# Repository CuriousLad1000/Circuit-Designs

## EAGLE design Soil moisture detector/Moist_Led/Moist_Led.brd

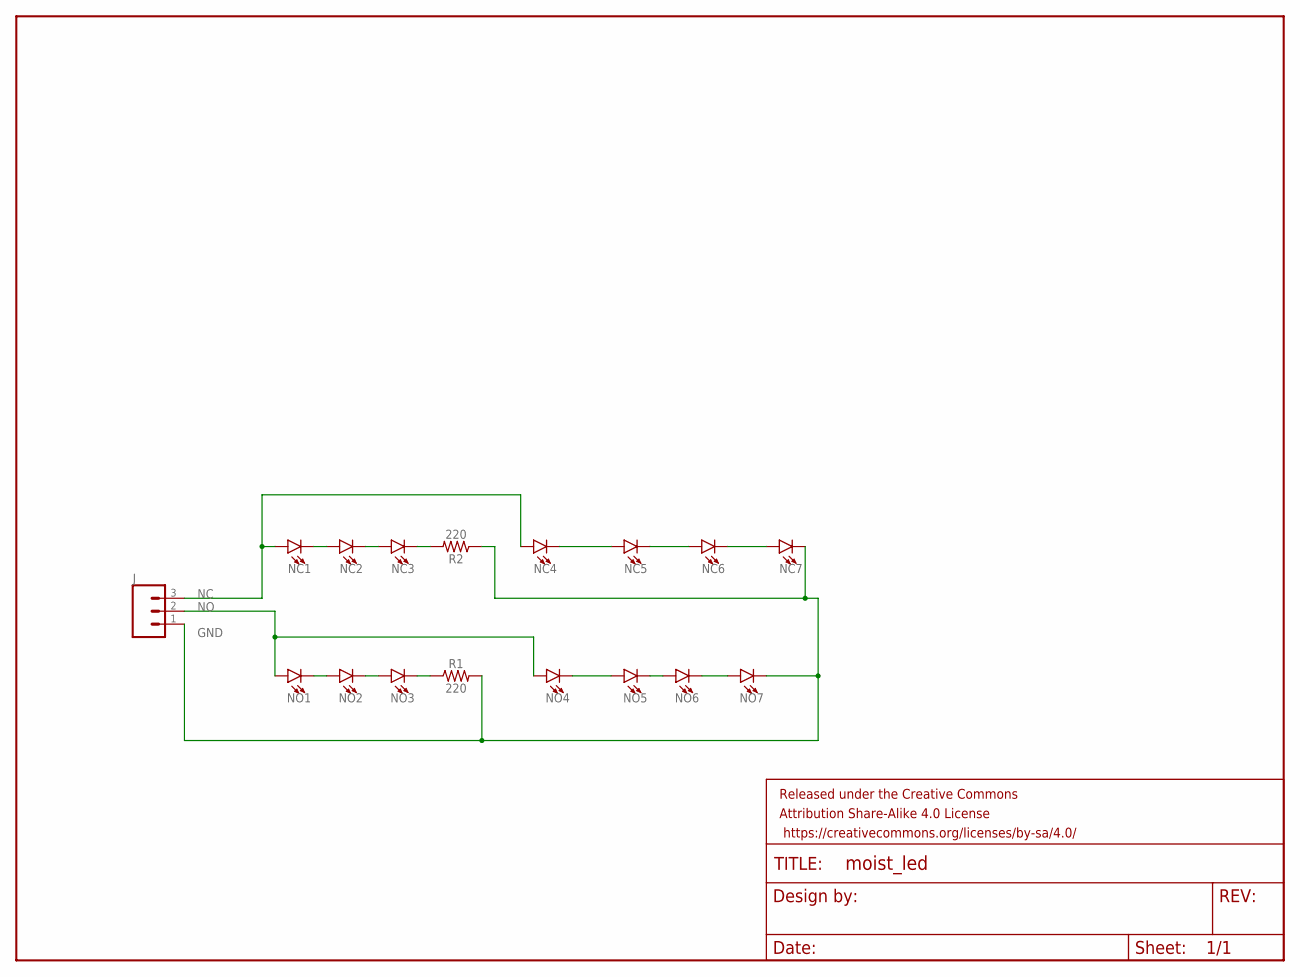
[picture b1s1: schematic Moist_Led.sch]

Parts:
FRAME1: FRAME-LETTER; CREATIVE_COMMONS
J: CONN_03; 1X03
NC1, NC2, NC3, NC4, NC5, NC6, NC7: LED5MM; LED_5MM
NO1, NO2, NO3, NO4, NO5, NO6, NO7: LED5MM; LED_5MM
R1, R2: 220; AXIAL-0.3

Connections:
GND: J.1, NC7.K (C), NO7.K (C), R1.P$2 (2), R2.P$1 (1)
unnamed: NO1.K (C), NO2.A
unnamed: NO2.K (C), NO3.A
unnamed: NC1.K (C), NC2.A
unnamed: NC2.K (C), NC3.A
unnamed: NC3.K (C), R2.P$2 (2)
unnamed: NC5.K (C), NC6.A
unnamed: NC6.K (C), NC7.A
unnamed: NO6.K (C), NO7.A
unnamed: NO5.K (C), NO6.A
unnamed: NO4.K (C), NO5.A
unnamed: NO3.K (C), R1.P$1 (1)
NC: J.3, NC1.A, NC4.A
NC4: NC4.K (C), NC5.A
NO: J.2, NO1.A, NO4.A

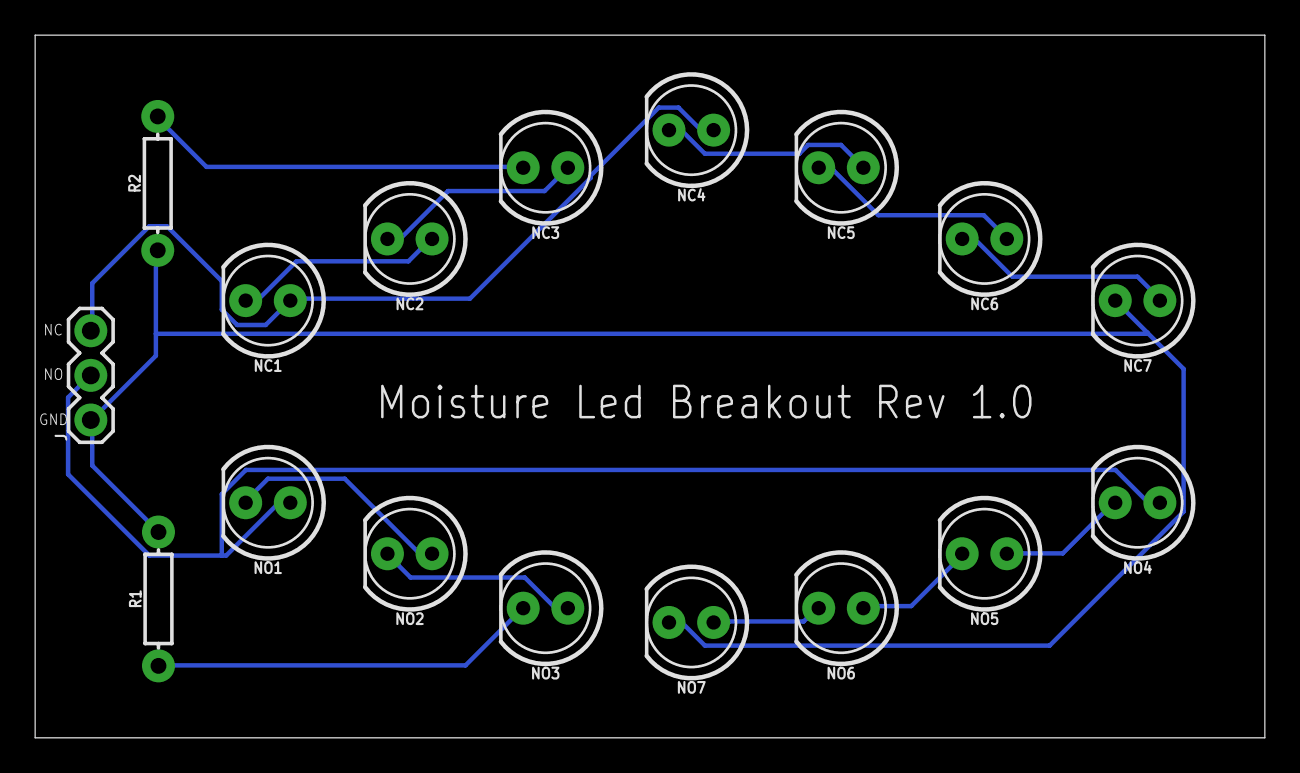
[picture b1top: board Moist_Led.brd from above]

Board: 2 copper layers, 70.0 x 40.0 mm, 18 parts (0 on the bottom side), 15 nets.

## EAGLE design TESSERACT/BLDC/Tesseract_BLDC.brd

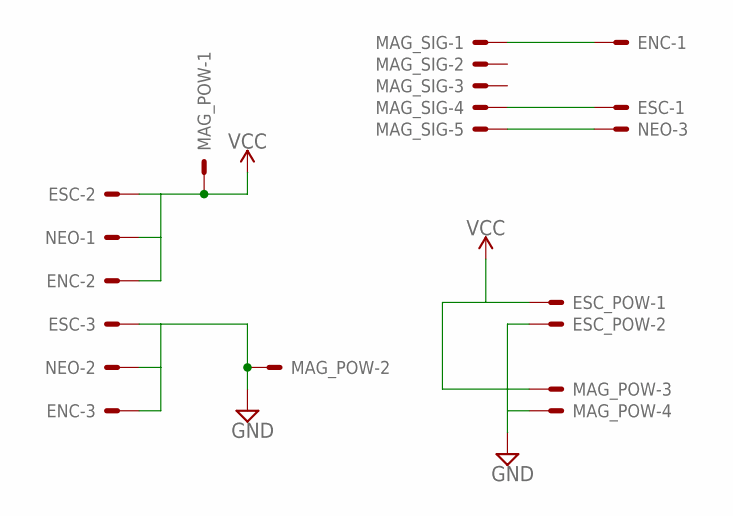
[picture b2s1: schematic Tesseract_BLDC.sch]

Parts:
ENC: JST-XH-03-PIN-LONG-PAD; JST-XH-03-PACKAGE-LONG-PAD
ESC: JST-XH-03-PIN-LONG-PAD; JST-XH-03-PACKAGE-LONG-PAD
ESC_POW: JST-XH-02-PIN-LONG-PAD; JST-XH-02-PACKAGE-LONG-PAD
MAG_POW: JST-XH-04-PIN-LONG-PAD; JST-XH-04-PACKAGE-LONG-PAD
MAG_SIG: JST-XH-05-PIN-LONG-PAD; JST-XH-05-PACKAGE-LONG-PAD
NEO: JST-XH-03-PIN-LONG-PAD; JST-XH-03-PACKAGE-LONG-PAD

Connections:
5V_GND: ENC.3, ESC.3, MAG_POW.2, NEO.2
5V_VCC: ENC.2, ESC.2, MAG_POW.1, NEO.1
12V_GND: ESC_POW.2, MAG_POW.4
12V_VCC: ESC_POW.1, MAG_POW.3
PIN3: ENC.1, MAG_SIG.1
PIN6: ESC.1, MAG_SIG.4
PIN7: MAG_SIG.5, NEO.3

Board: 2 copper layers, 6 parts (0 on the bottom side), 7 nets, no tracks yet.

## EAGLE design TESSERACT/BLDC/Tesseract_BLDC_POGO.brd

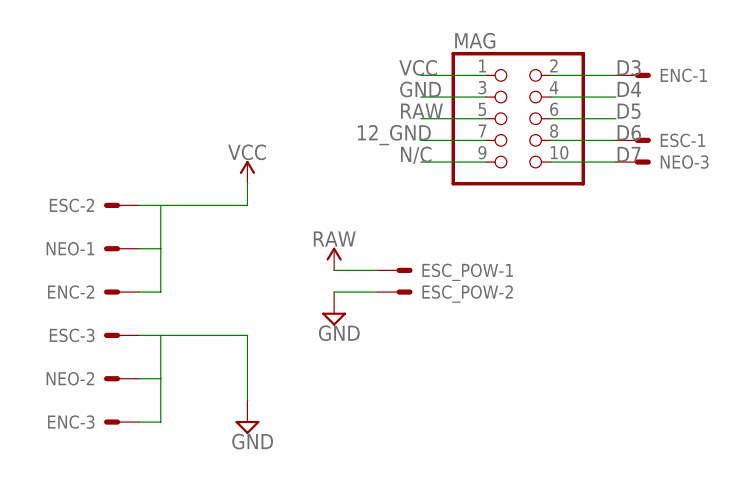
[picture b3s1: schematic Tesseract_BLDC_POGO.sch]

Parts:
ENC: JST-XH-03-PIN-LONG-PAD; JST-XH-03-PACKAGE-LONG-PAD
ESC: JST-XH-03-PIN-LONG-PAD; JST-XH-03-PACKAGE-LONG-PAD
ESC_POW: JST-XH-02-PIN-LONG-PAD; JST-XH-02-PACKAGE-LONG-PAD
MAG: PINHD-2X5; 2X05
NEO: JST-XH-03-PIN-LONG-PAD; JST-XH-03-PACKAGE-LONG-PAD

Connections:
12_GND: ESC_POW.2, MAG.7
D3: ENC.1, MAG.2
D4: MAG.4
D5: MAG.6
D6: ESC.1, MAG.8
D7: MAG.10, NEO.3
GND: ENC.3, ESC.3, MAG.3, NEO.2
N/C: MAG.9
RAW: ESC_POW.1, MAG.5
VCC: ENC.2, ESC.2, MAG.1, NEO.1

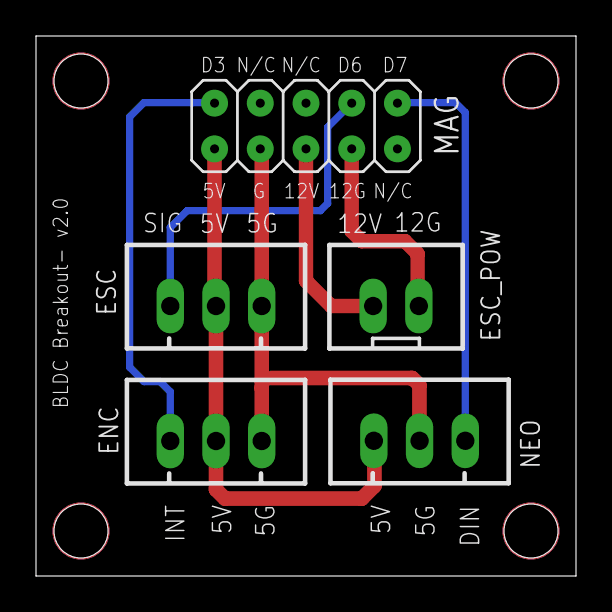
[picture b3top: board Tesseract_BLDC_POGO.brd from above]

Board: 2 copper layers, 30.0 x 30.0 mm, 5 parts (0 on the bottom side), 7 nets.

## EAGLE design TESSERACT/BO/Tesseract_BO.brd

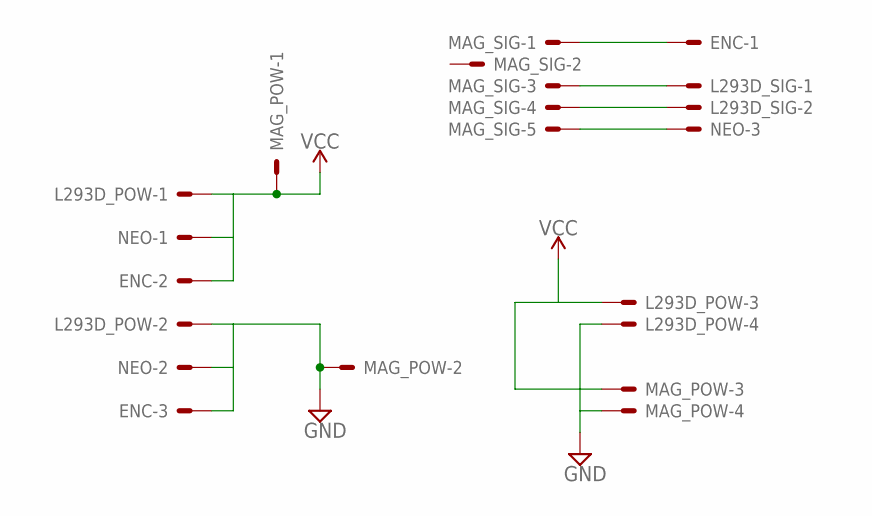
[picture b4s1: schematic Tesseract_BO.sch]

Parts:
ENC: JST-XH-03-PIN-LONG-PAD; JST-XH-03-PACKAGE-LONG-PAD
L293D_POW: JST-XH-04-PIN-LONG-PAD; JST-XH-04-PACKAGE-LONG-PAD
L293D_SIG: JST-XH-02-PIN-LONG-PAD; JST-XH-02-PACKAGE-LONG-PAD
MAG_POW: JST-XH-04-PIN-LONG-PAD; JST-XH-04-PACKAGE-LONG-PAD
MAG_SIG: JST-XH-05-PIN-LONG-PAD; JST-XH-05-PACKAGE-LONG-PAD
NEO: JST-XH-03-PIN-LONG-PAD; JST-XH-03-PACKAGE-LONG-PAD

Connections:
5V_GND: ENC.3, L293D_POW.2, MAG_POW.2, NEO.2
5V_VCC: ENC.2, L293D_POW.1, MAG_POW.1, NEO.1
12V_GND: L293D_POW.4, MAG_POW.4
12V_VCC: L293D_POW.3, MAG_POW.3
PIN3: ENC.1, MAG_SIG.1
PIN5: L293D_SIG.1, MAG_SIG.3
PIN6: L293D_SIG.2, MAG_SIG.4
PIN7: MAG_SIG.5, NEO.3

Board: 2 copper layers, 6 parts (0 on the bottom side), 8 nets, no tracks yet.

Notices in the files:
parts and their libraries:
SparkFun-LED: Licensing: Creative Commons ShareAlike 4.0 International - https://creativecommons.org/licenses/by-sa/4.0
SparkFun-Aesthetics: Released under the Creative Commons Attribution Share-Alike 4.0 License
SparkFun-Aesthetics: https://creativecommons.org/licenses/by-sa/4.0
